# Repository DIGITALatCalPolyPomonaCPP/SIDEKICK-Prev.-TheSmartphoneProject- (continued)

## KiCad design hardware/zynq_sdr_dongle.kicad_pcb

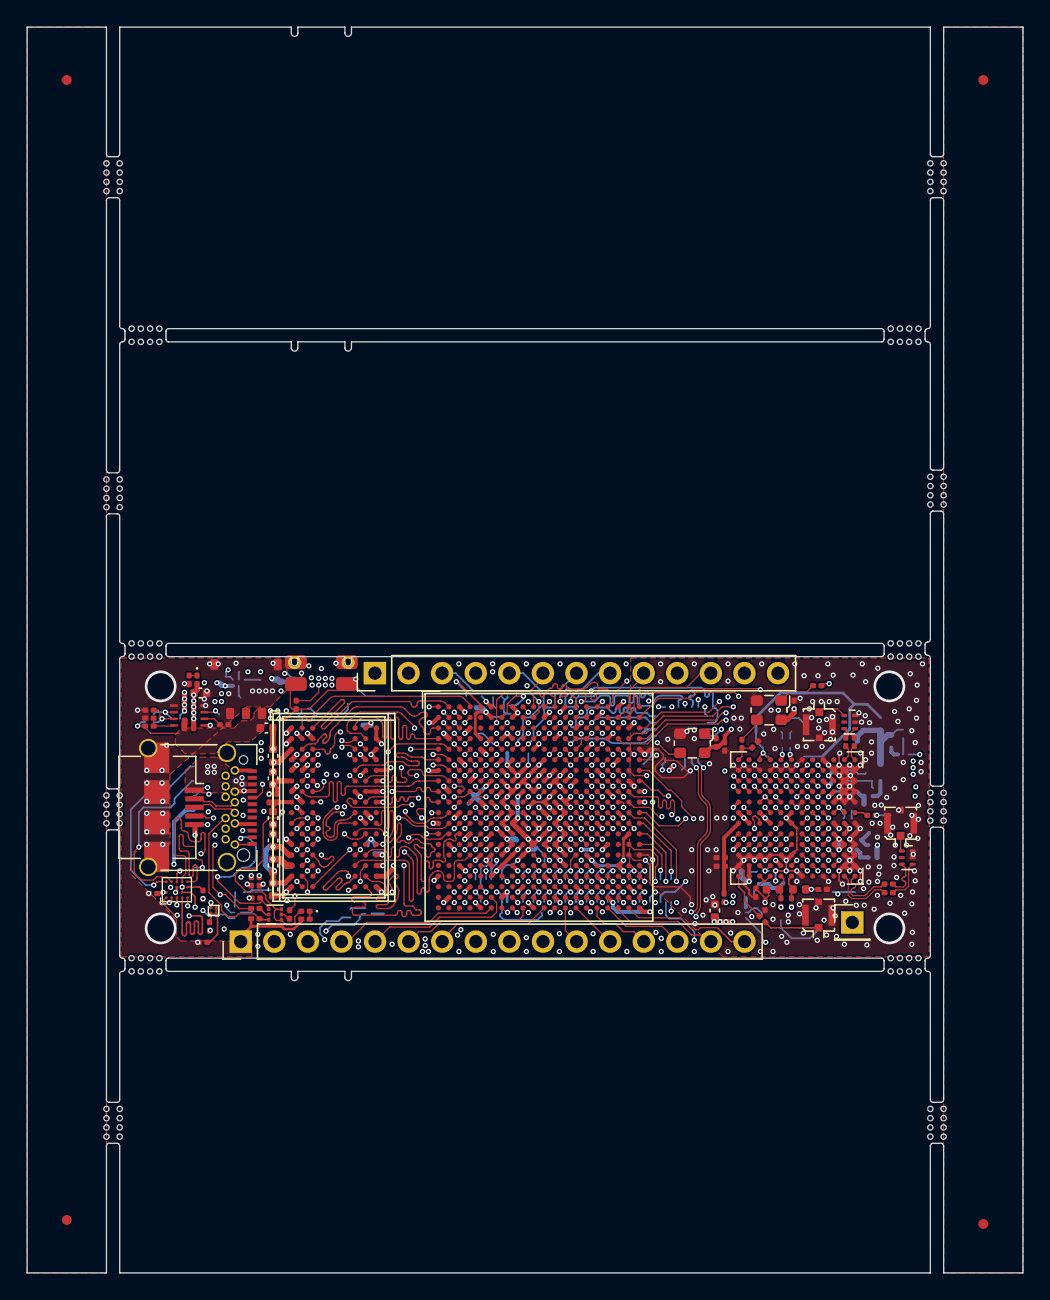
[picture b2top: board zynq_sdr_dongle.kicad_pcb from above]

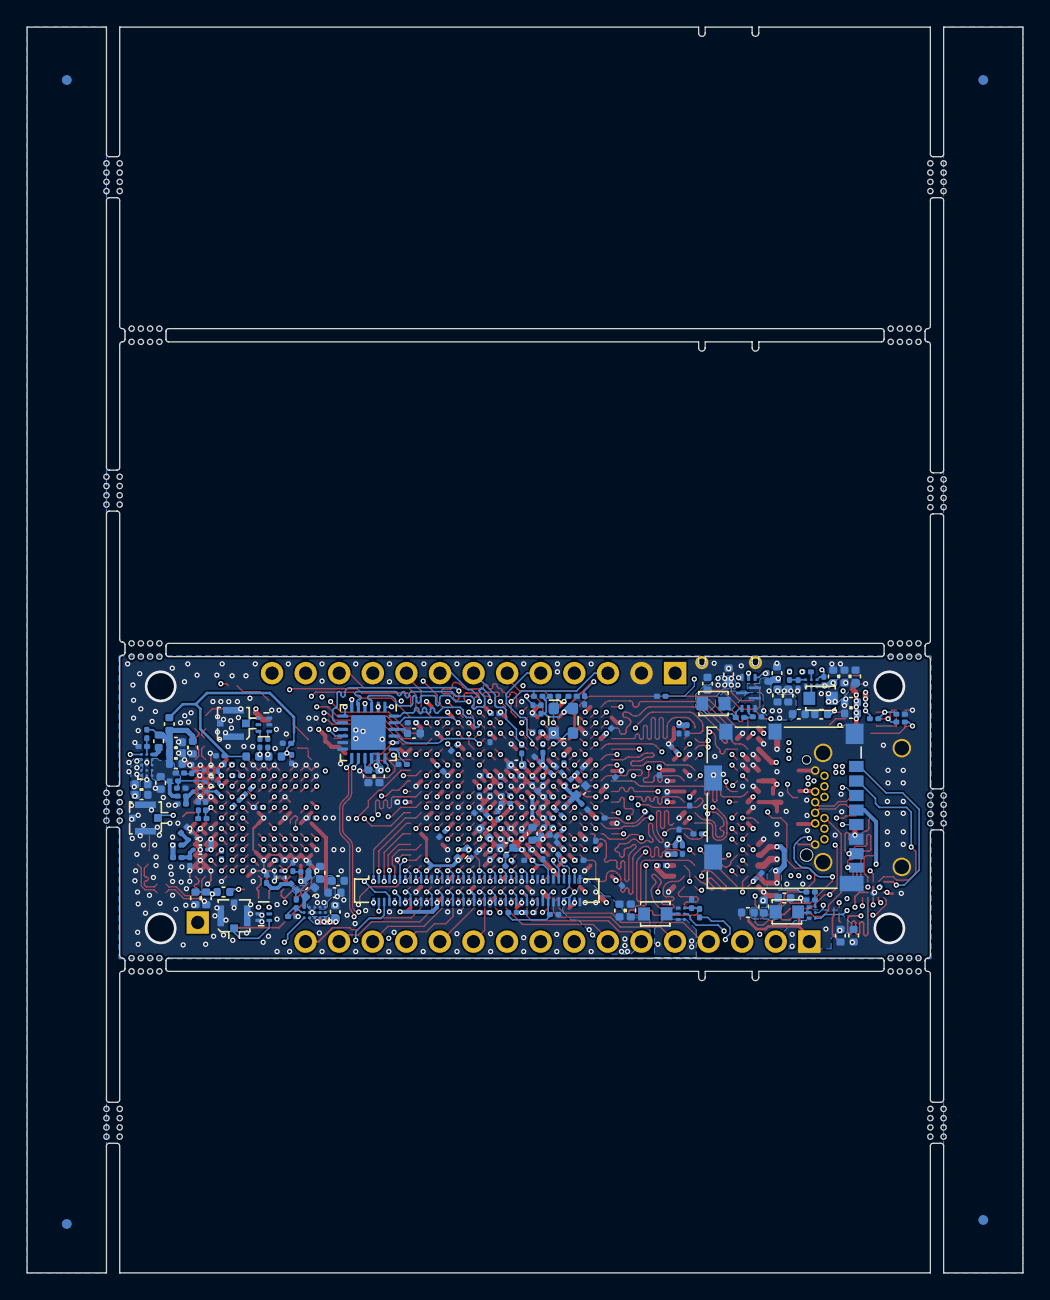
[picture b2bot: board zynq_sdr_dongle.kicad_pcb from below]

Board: 6 copper layers, 75.3 x 94.2 mm, 285 parts (208 on the bottom side), 328 nets.

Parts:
C1, C6, C9, C12, C80, C81: 18pF; C_0201_0603Metric
C2, C10, C13, C22, C28, C29, C36, C41, C62, C63, C78, C79, C120, C124, C125: 0.1uF; C_0402_1005Metric
C3, C4, C5, C7, C8, C11, C14, C15, C16, C17, C18, C19, C20, C21, C24, C25, C26, C31, C33, C34, C38, C44, C45, C46, C47, C52, C53, C54, C55, C56, C57, C58, C59, C60, C61, C64, C65, C66, C67, C68, C69, C70, C71, C72, C73, C74, C75, C76, C77, C83, C84, C85, C86, C87, C88, C98, C99, C100, C107, C108, C109, C110, C111, C115, C116, C117, C130, C131, C132, C133, C134, C135, C136, C137, C138, C139, C140, C141, C142, C143, C144, C145, C146, C147, C148: 0.1uF; C_0201_0603Metric
C23, C27, C30, C32, C35, C37, C39, C40, C42, C43, C48, C49, C50, C51, C89, C90, C91, C92, C93, C94, C95, C96, C97, C101, C102, C118, C119, C123, C128: 4.7uF; C_0402_1005Metric
C82, C104, C105, C112, C113, C114: NFM15PC146R0G3D; C_0402_1005Metric
C103, C106, C129: 1uF; C_0402_1005Metric
C121, C122, C126, C127: 10nF; C_0402_1005Metric
D1, D2, D3: LED; LED_0201_0603Metric
D4, D5: TVS; R_0201_0603Metric
FB1, FB9: FerriteBead_Small; C_0402_1005Metric
FB2, FB3, FB4, FB5, FB6, FB7, FB8: FerriteBead_Small; C_0201_0603Metric
FID1, FID2, FID3, FID4, FID5, FID6, FID7, FID8: Fiducial; Fiducial_0.75mm_Mask2.25mm
FL1, FL2, FL3, FL4: 0850BM14E0016; Balun_Johanson_1.6x0.8mm
J1: USB_C_Receptacle; USB_C_Receptacle_Amphenol_12401548E4-2A_CircularHoles
J2: USB_B_Micro; USB_Micro-B_Amphenol_10104110_Horizontal
J3: Micro_SD_Card; microSD_HC_Molex_104031-0811
J4: 5024268012; Molex_SlimStack_502430-8010_2x40_P0.40mm_Vertical
J5, J6, J7, J8, J9, J12: Conn_Coaxial; U.FL_Molex_MCRF_73412-0110_Vertical
J10: Conn_01x13_Male; PinHeader_1x13_P2.54mm_Vertical
J11: Conn_01x16_Male; PinHeader_1x16_P2.54mm_Vertical
J13: Conn_01x04_Male; BM03B-ACHSS-GAN-TF
J14: Conn_01x01; PinHeader_1x01_P2.54mm_Vertical
L1, L6, L7, L8: DFE18SANR47MG0; L_Murata_LQH2MCNxxxx02_2.0x1.6mm
L2, L3, L4, L5: L; L_0402_1005Metric
Q1: Q_Dual_NMOS_PMDXB600UNE; DFN-6-1EP_1.2x1.2mm_P0.4mm_EP0.3x0.94mm_PullBack
Q2: PMCM4401VNE; WLCSP-4-X1-WLB0909-4_0.89x0.89mm_P0.5mm
R1, R4, R5: 80Ω; R_0201_0603Metric
R2, R47, R48, R55, R56, R59, R70, R71: 4.7K; R_0201_0603Metric
R3, R43: 240Ω; R_0201_0603Metric
R6, R37: 23.7K; R_0201_0603Metric
R7, R30, R38: 5K; R_0201_0603Metric
R8, R19, R22, R25, R46, R49, R50, R52, R62, R65, R66, R69: 10K; R_0201_0603Metric
R9: 82K; R_0201_0603Metric
R10: 18K; R_0201_0603Metric
R11, R12, R18: 14.3K; R_0201_0603Metric
R13, R15: 360K; R_0201_0603Metric
R14, R16: 300K; R_0201_0603Metric
R17: 8.06K; R_0201_0603Metric
R20: 200K; R_0201_0603Metric
R21: 100K; R_0201_0603Metric
R23: 51.7K; R_0201_0603Metric
R24: 41.2K; R_0201_0603Metric
R26: 22K; R_0201_0603Metric
R27: 33K; R_0201_0603Metric
R28, R53, R64, R67: 0R; R_0201_0603Metric
R29: 10.2K; R_0201_0603Metric
R31, R32, R33, R34, R35, R36, R40: 1K; R_0201_0603Metric
R39: 51.1K; R_0201_0603Metric
R41: 0R; R_0402_1005Metric
R42, R51, R54, R60, R61, R63, R68: N/A; R_0201_0603Metric
R44, R45: 500Ω; R_0201_0603Metric
R57, R58: 30R; R_0201_0603Metric
SW2: SW_DIP_x01; EVQ9P701P
U1: DDR3; BGA-96_9.0x13.0mm_Layout2x3x16_P0.8mm_NoPaste
U2: xc7z020clg400; Xilinx_CLG400_020_Delay
U3: AD9361; bga-100_10_10_1p32_0p8
U4, U9, U10: TPS62088; PowerWCSP-6
U5: USB3346; QFN-24-1EP_4x4mm_P0.5mm_EP2.6x2.6mm
U6, U7: MAX38904C; wlp-15_2p168_1p338_0p5_0p4
U8: TPS62867; VQFN-HR
U11: TPS2121; VQFN-12_2p0_2p5_0p5
U13: TXS0206A; WLCSP-20_1.609x1.994mm_Layout4x5_P0.4mm
X1, X2, X3: SiT1602B; Oscillator_SMD_ECS_2520MV-xxx-xx-4Pin_2.5x2.0mm

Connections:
+1V0: C50.1, C51.1, C52.1, C53.1, C54.1, C55.1, C56.1, C57.1, C58.1, C59.1, C60.1, C61.1, C62.1, C63.1, C64.1, C65.1, J4.74, J4.80, L7.1, R26.1, U2.G7 (VCCPINT[6]), U2.G11 (VCCBRAM[2]), U2.G13 (VCCINT[9]), U2.H10 (VCCBRAM[2]), U2.H12 (VCCINT[9]), U2.J7 (VCCPINT[6]), U2.J13 (VCCINT[9]), U2.K12 (VCCINT[9]), U2.L7 (VCCPINT[6]), U2.L13 (VCCINT[9]), U2.M12 (VCCINT[9]), U2.N7 (VCCPINT[6]), U2.N13 (VCCINT[9]), U2.P8 (VCCPINT[6]), U2.P12 (VCCINT[9]), U2.R7 (VCCPINT[6]), U2.R13 (VCCINT[9])
+1V8: C23.1, C27.1, C30.1, C32.1, C35.1, C37.1, C66.1, C67.1, C68.1, C69.1, C70.1, C71.1, C72.1, C73.1, C74.1, C75.1, C76.1, C77.1, C78.1, C79.1, C117.1, C130.1, C131.1, C132.1, C133.1, C134.1, C135.1, C138.1, C139.1, C140.1, C141.1, C142.1, C143.1, C144.1, C145.1, C146.1, C148.1, J4.67, L1.1, R20.1, R22.1, R41.1, R46.1, R47.1, R48.1, R49.1, R50.2, R59.2, R62.1, R65.1, R66.1, R69.1, R70.2, R71.2, U2.A6 (PS_MIO5_500), U2.A13 (VCCO_MIO1_501[4]), U2.B6 (VCCO_MIO0_500[2]), U2.B16 (VCCO_MIO1_501[4]), U2.C19 (VCCO_35[6]), U2.D5 (PS_MIO8_500), U2.D7 (VCCO_MIO0_500[2]), U2.D8 (PS_MIO7_500), U2.D12 (VCCO_MIO1_501[4]), U2.E15 (VCCO_MIO1_501[4]), U2.F8 (VCCPAUX[5]), U2.F18 (VCCO_35[6]), U2.G8 (VCCPLL), U2.G9 (VCCPAUX[5]), U2.H8 (VCCPAUX[5]), U2.H14 (VCCO_35[6]), U2.J9 (VCCADC_0), U2.J11 (VCCAUX[6]), U2.J17 (VCCO_35[6]), U2.K6 (VCCO_0), U2.K8 (VCCPAUX[5]), U2.K20 (VCCO_35[6]), U2.L11 (VCCAUX[6]), U2.M8 (VCCPAUX[5]), U2.M16 (VCCO_35[6]), U2.N6 (RSVDVCC3), U2.N9 (VCCAUX[6]), U2.N11 (VCCAUX[6]), U2.P10 (VCCAUX[6]), U2.R6 (RSVDVCC2), U2.R9 (VCCAUX[6]), U2.T6 (RSVDVCC1), U3.B8 (Vdd_GPO), U3.H12 (Vdd_INTERFACE), U6.A1 (IN), U6.A2 (IN), U6.A3 (IN), U6.A4 (IN), U7.A1 (IN), U7.A2 (IN), U7.A3 (IN), U7.A4 (IN), U8.8 (VOS), U13.A2 (VCCA), X1.4 (VDD), X2.4 (VDD), X3.4 (VDD)
+3V3: C96.1, C97.1, C147.1, J3.4 (VDD), J10.1, L8.1, R9.1, U13.B3 (VCCB)
+5V: C43.1, C89.1, C90.1, C91.1, C92.1, C93.1, C94.1, C95.1, C102.1, C118.1, C119.1, D1.2 (A), D3.2 (A), R8.1, R19.1, R25.1, U4.A2 (VIN), U5.16 (VBAT), U5.17 (VBUS), U8.3 (VIN), U9.A2 (VIN), U10.A1 (EN), U10.A2 (VIN), U11.1 (OUT), U11.8 (OUT)
/ARD_ANALOG0: J11.2, U2.Y7 (IO_L13P_T2_MRCC_13)
/ARD_ANALOG1: J11.4, U2.Y6 (IO_L13N_T2_MRCC_13)
/ARD_ANALOG2: J11.5, U2.W6 (IO_L22N_T3_13)
/ARD_ANALOG3: J11.6, U2.Y9 (IO_L14P_T2_SRCC_13)
/ARD_ANALOG4: J11.7, U2.Y11 (IO_L18N_T2_13)
/ARD_ANALOG5: J11.8, R60.1, U2.Y12 (IO_L20P_T3_13)
/ARD_ANALOG6: J11.9, R42.1
/ARD_ANALOG7: J11.10, R61.1
/ARD_AREF: J11.3, R54.2, R63.2
/ARD_PWM2: J11.16, U2.Y19 (IO_L17N_T2_34)
/ARD_PWM3: J11.15, U2.Y18 (IO_L17P_T2_34)
/ARD_PWM4: J11.14, U2.Y17 (IO_L7N_T1_34)
/ARD_PWM5: J11.13, U2.Y16 (IO_L7P_T1_34)
/ARD_PWM6: J11.12, U2.Y14 (IO_L8N_T1_34)
/ARD_PWM7: J11.11, U2.Y13 (IO_L20N_T3_13)
/BTB Connector/FPGA_AUXADC_N: J4.59, U2.L10 (VN_0)
/BTB Connector/FPGA_AUXADC_P: J4.61, U2.K9 (VP_0)
/BTB Connector/FPGA_JTAG_TCK: J4.71, U2.F9 (TCK_0)
/BTB Connector/FPGA_JTAG_TDI: J4.73, R71.1, U2.G6 (TDI_0)
/BTB Connector/FPGA_JTAG_TDO: J4.77, U2.F6 (TDO_0)
/BTB Connector/FPGA_JTAG_TMS: J4.75, R70.1, U2.J6 (TMS_0)
/BTB Connector/TRANS_GPO_0: J4.8, U3.B7 (GPO_0)
/BTB Connector/TRANS_GPO_1: J4.2, U3.B6 (GPO_1)
/BTB Connector/TRANS_GPO_2: J4.4, U3.B5 (GPO_2)
/BTB Connector/TRANS_GPO_3: J4.6, U3.B4 (GPO_3)
/FPGA_VREF: J4.68, R53.2, R54.1, U2.L9 (VREFP_0)
/LDO_EN: R64.2, U2.B13 (PS_MIO50_501), U6.A5 (EN), U7.A5 (EN)
/PS-SRST#: J10.3, R62.2, U2.B10 (PS_SRST_B_501)
/PS_MIO10_SCL: J10.7, R66.2, U2.E9 (PS_MIO10_500)
/PS_MIO11_SDA: J10.6, R65.2, U2.C6 (PS_MIO11_500)
/PS_MIO16_SPI_CLK: J10.9, U2.A19 (PS_MIO16_501)
/PS_MIO17_SPI_MISO: J10.10, U2.E14 (PS_MIO17_501)
/PS_MIO18_SPI_SS: J10.11, U2.B18 (PS_MIO18_501)
/PS_MIO19_SPI_MOSI: J10.8, U2.D10 (PS_MIO19_501)
/PS_MIO20_SPI_SS1: J10.12, U2.A17 (PS_MIO20_501)
/PS_MIO21_SPI_SS2: J10.13, U2.F14 (PS_MIO21_501)
/Power Manage/DCDC_PG_1V0: R25.2, U8.4 (EN), U10.B1 (PG)
/Power Manage/DCDC_PG_1V8: R19.2, U4.A1 (EN), U8.5 (PG), U9.A1 (EN)
/Power Manage/DCDC_PG_1V35: C38.1, R22.2, SW2.2, U2.C7 (PS_POR_B_500), U9.B1 (PG)
/TRANS_AUX_ADC: R61.2, U3.L5 (AUXADC)
/TRANS_AUX_DAC1: R42.2, U3.B3 (AUXDAC1)
/TRANS_AUX_DAC2: R60.2, U3.C3 (AUXDAC2)
/Transceiver Powr/RX_VCO: C6.1, R11.1, U3.G2 (RX_VCO_LDO_OUT), U3.G3 (VddA1P1_RX_VCO)
/Transceiver Powr/TX_VCO: C12.1, R12.1, U3.A11 (VddA1P1_TX_VCO), U3.B11 (TX_VCO_LDO_OUT)
/Transceiver Powr/VDDA_BB: C114.3, U3.K4 (VddA1P3_BB)
/Transceiver Powr/VDDA_DIGI_1V3: C136.1, C137.1, FB8.1, U3.F12 (VddD1P3_DIG)
/Transceiver Powr/VDDA_RX_LO: C113.3, U3.E2 (VddA1P3_RX_LO), U3.F2 (VddA1P3_RX_VCO_LDO)
/Transceiver Powr/VDDA_RX_SYNTH: C82.3, U3.J3 (VddA1P3_RX_SYNTH)
/Transceiver Powr/VDDA_RX_TX: C104.3, U3.D2 (VddA1P3_RX_RF), U3.D3 (VddA1P3_RX_TX), U3.E3 (VddA1P3_TX_LO_BUFFER)
/Transceiver Powr/VDDA_TX_LO: C112.3, U3.B9 (VddA1P3_TX_LO), U3.B10 (VddA1P3_TX_VCO_LDO)
/Transceiver Powr/VDDA_TX_SYNTH: C105.3, U3.K3 (VddA1P3_TX_SYNTH)
/Transceiver RF/EXT_SYNC: J14.1, R68.1
/Transceiver RF/TRANS_CMOS_FB_CLK: U2.K18 (IO_L12N_T1_MRCC_35), U3.F10 (FB_CLK+)
/Transceiver RF/TRANS_CMOS_RX_D0: U2.E17 (IO_L3P_T0_DQS_AD1P_35), U3.K11 (P1_D0/RX_D0-)
/Transceiver RF/TRANS_CMOS_RX_D1: U2.F16 (IO_L6P_T0_35), U3.J12 (P1_D1/RX_D0+)
/Transceiver RF/TRANS_CMOS_RX_D2: U2.J20 (IO_L17P_T2_AD5P_35), U3.K10 (P1_D2/RX_D1-)
/Transceiver RF/TRANS_CMOS_RX_D3: U2.F17 (IO_L6N_T0_VREF_35), U3.J11 (P1_D3/RX_D1+)
/Transceiver RF/TRANS_CMOS_RX_D4: U2.F20 (IO_L15N_T2_DQS_AD12N_35), U3.K9 (P1_D4/RX_D2-)
/Transceiver RF/TRANS_CMOS_RX_D5: U2.G15 (IO_L19N_T3_VREF_35), U3.J10 (P1_D5/RX_D2+)
/Transceiver RF/TRANS_CMOS_RX_D6: U2.G19 (IO_L18P_T2_AD13P_35), U3.K8 (P1_D6/RX_D3-)
/Transceiver RF/TRANS_CMOS_RX_D7: U2.G17 (IO_L16P_T2_35), U3.J9 (P1_D7/RX_D3+)
/Transceiver RF/TRANS_CMOS_RX_D8: U2.E18 (IO_L5P_T0_AD9P_35), U3.K7 (P1_D8/RX_D4-)
/Transceiver RF/TRANS_CMOS_RX_D9: U2.G18 (IO_L16N_T2_35), U3.J8 (P1_D9/RX_D4+)
/Transceiver RF/TRANS_CMOS_RX_D10: U2.E19 (IO_L5N_T0_AD9N_35), U3.J7 (P1_D10/RX_D5-)
/Transceiver RF/TRANS_CMOS_RX_D11: U2.H18 (IO_L14N_T2_AD4N_SRCC_35), U3.H8 (P1_D11/RX_D5+)
/Transceiver RF/TRANS_CMOS_RX_FRAME: U2.H17 (IO_L13N_T2_MRCC_35), U3.G8 (RX_FRAME+)
/Transceiver RF/TRANS_CMOS_TX_D0: U2.M18 (IO_L8N_T1_AD10N_35), U3.E12 (P0_D0/TX_D0-)
/Transceiver RF/TRANS_CMOS_TX_D1: U2.L17 (IO_L11N_T1_SRCC_35), U3.D11 (P0_D1/TX_D0+)
/Transceiver RF/TRANS_CMOS_TX_D2: U2.M19 (IO_L7P_T1_AD2P_35), U3.E11 (P0_D2/TX_D1-)
/Transceiver RF/TRANS_CMOS_TX_D3: U2.M15 (IO_L23N_T3_35), U3.D10 (P0_D3/TX_D1+)
/Transceiver RF/TRANS_CMOS_TX_D4: U2.K16 (IO_L24P_T3_AD15P_35), U3.E10 (P0_D4/TX_D2-)
/Transceiver RF/TRANS_CMOS_TX_D5: U2.M17 (IO_L8P_T1_AD10P_35), U3.D9 (P0_D5/TX_D2+)
/Transceiver RF/TRANS_CMOS_TX_D6: U2.J16 (IO_L24N_T3_AD15N_35), U3.E9 (P0_D6/TX_D3-)
/Transceiver RF/TRANS_CMOS_TX_D7: U2.N16 (IO_L21N_T3_DQS_AD14N_35), U3.D8 (P0_D7/TX_D3+)
/Transceiver RF/TRANS_CMOS_TX_D8: U2.L16 (IO_L11P_T1_SRCC_35), U3.E8 (P0_D8/TX_D4-)
/Transceiver RF/TRANS_CMOS_TX_D9: U2.M14 (IO_L23P_T3_35), U3.D7 (P0_D9/TX_D4+)
/Transceiver RF/TRANS_CMOS_TX_D10: U2.H15 (IO_L19P_T3_35), U3.F8 (P0_D10/TX_D5-)
/Transceiver RF/TRANS_CMOS_TX_D11: U2.K19 (IO_L10P_T1_AD11P_35), U3.E7 (P0_D11/TX_D5+)
/Transceiver RF/TRANS_CMOS_TX_FRAME: U2.J19 (IO_L10N_T1_AD11N_35), U3.G9 (TX_FRAME+)
/Transceiver RF/TRANS_CTRL_IN0: U2.L14 (IO_L22P_T3_AD7P_35), U3.C5 (CTRL_IN0)
/Transceiver RF/TRANS_CTRL_IN1: U2.L15 (IO_L22N_T3_AD7N_35), U3.C6 (CTRL_IN1)
/Transceiver RF/TRANS_CTRL_IN2: U2.J15 (IO_25_35), U3.D6 (CTRL_IN2)
/Transceiver RF/TRANS_CTRL_IN3: U2.K14 (IO_L20P_T3_AD6P_35), U3.D5 (CTRL_IN3)
/Transceiver RF/TRANS_CTRL_OUT0: U2.B20 (IO_L1N_T0_AD0N_35), U3.D4 (CTRL_OUT0)
/Transceiver RF/TRANS_CTRL_OUT1: U2.A20 (IO_L2N_T0_AD8N_35), U3.E4 (CTRL_OUT1)
/Transceiver RF/TRANS_CTRL_OUT2: U2.J14 (IO_L20N_T3_AD6N_35), U3.E5 (CTRL_OUT2)
/Transceiver RF/TRANS_CTRL_OUT3: U2.C20 (IO_L1P_T0_AD0P_35), U3.E6 (CTRL_OUT3)
/Transceiver RF/TRANS_CTRL_OUT4: U2.G20 (IO_L18N_T2_AD13N_35), U3.F6 (CTRL_OUT4)
/Transceiver RF/TRANS_CTRL_OUT5: U2.N15 (IO_L21P_T3_DQS_AD14P_35), U3.F5 (CTRL_OUT5)
/Transceiver RF/TRANS_CTRL_OUT6: U2.L20 (IO_L9N_T1_DQS_AD3N_35), U3.F4 (CTRL_OUT6)
/Transceiver RF/TRANS_CTRL_OUT7: U2.D19 (IO_L4P_T0_35), U3.G4 (CTRL_OUT7)
/Transceiver RF/TRANS_ENABLE: U2.D18 (IO_L3N_T0_DQS_AD1N_35), U3.G6 (ENABLE)
/Transceiver RF/TRANS_ENAGC: U2.J18 (IO_L14P_T2_AD4P_SRCC_35), U3.G5 (EN_AGC)
/Transceiver RF/TRANS_MRCC_CLKOUT: U2.H16 (IO_L13P_T2_MRCC_35), U3.J6 (CLK_OUT)
/Transceiver RF/TRANS_MRCC_DATA_CLK: U2.K17 (IO_L12P_T1_MRCC_35), U3.G11 (DATA_CLK+)
/Transceiver RF/TRANS_OSC_N: C81.1, X3.3 (OUT)
/Transceiver RF/TRANS_RBIAS: R18.1, U3.L4 (RBIAS)
/Transceiver RF/TRANS_RST: U2.B14 (PS_MIO47_501), U3.K5 (~RESET)
/Transceiver RF/TRANS_RXRF0_N: C108.1, FL3.3 (RF_N)
/Transceiver RF/TRANS_RXRF0_P: C107.1, FL3.4 (RF_P)
/Transceiver RF/TRANS_RXRF1_N: C116.1, FL4.3 (RF_N)
/Transceiver RF/TRANS_RXRF1_P: C115.1, FL4.4 (RF_P)
/Transceiver RF/TRANS_SPI_CLK: U2.A16 (PS_MIO24_501), U3.J5 (SPI_CLK)
/Transceiver RF/TRANS_SPI_MISO: U2.D11 (PS_MIO23_501), U3.L6 (SPI_MISO)
/Transceiver RF/TRANS_SPI_MOSI: U2.B17 (PS_MIO22_501), U3.J4 (SPI_MOSI)
/Transceiver RF/TRANS_SPI_SS: U2.F15 (PS_MIO25_501), U3.K6 (SPI_~EN)
/Transceiver RF/TRANS_SYNC: R67.1, U2.H20 (IO_L17N_T2_AD5N_35)
/Transceiver RF/TRANS_TXNRX: U2.D20 (IO_L4N_T0_35), U3.H4 (TX~RX)
/Transceiver RF/TRANS_TXRF0_N: C44.1, FL1.4 (RF_P)
/Transceiver RF/TRANS_TXRF0_P: C45.1, FL1.3 (RF_N)
/Transceiver RF/TRANS_TXRF1_N: C47.1, FL2.4 (RF_P)
/Transceiver RF/TRANS_TXRF1_P: C46.1, FL2.3 (RF_N)
/UART_RX: J10.5, U2.E8 (PS_MIO13_500)
/UART_TX: J10.4, U2.D9 (PS_MIO12_500)
/USB Connector/PS_MIO27_500_USB_RESETB: U2.D13 (PS_MIO27_501), U5.21 (~RESETB)
/USB Connector/PS_MIO29_501_USB0_DIR: U2.C13 (PS_MIO29_501), U5.24 (DIR)
/USB Connector/PS_MIO30_501_USB0_STP: U2.C15 (PS_MIO30_501), U5.23 (STP)
/USB Connector/PS_MIO31_501_USB0_NXT: U2.E16 (PS_MIO31_501), U5.2 (NXT)
/USB Connector/PS_MIO36_501_USB0_CLK: U2.A11 (PS_MIO36_501), U5.1 (CLKOUT)
/USB Connector/PS_MIO_501_USB0_D0: U2.A14 (PS_MIO32_501), U5.3 (DATA0)
/USB Connector/PS_MIO_501_USB0_D1: U2.D15 (PS_MIO33_501), U5.4 (DATA1)
/USB Connector/PS_MIO_501_USB0_D2: U2.A12 (PS_MIO34_501), U5.5 (DATA2)
/USB Connector/PS_MIO_501_USB0_D3: U2.F12 (PS_MIO35_501), U5.6 (DATA3)
/USB Connector/PS_MIO_501_USB0_D4: U2.C16 (PS_MIO28_501), U5.7 (DATA4)
/USB Connector/PS_MIO_501_USB0_D5: U2.A10 (PS_MIO37_501), U5.8 (DATA5)
/USB Connector/PS_MIO_501_USB0_D6: U2.E13 (PS_MIO38_501), U5.9 (DATA6)
/USB Connector/PS_MIO_501_USB0_D7: U2.C18 (PS_MIO39_501), U5.10 (DATA7)
/USB Connector/PWR_STA: D2.2 (A), Q1.1 (G), Q1.3 (G), U11.9 (ST)
/USB Connector/SS_SET: C129.1, U11.11 (SS)
/USB Connector/USBC_CC1: J1.A5 (CC1), Q1.4 (D), R55.2
/USB Connector/USBC_CC2: J1.B5 (CC2), Q1.6 (D), R56.2
/USB Connector/USBHS_DN: D5.1 (A1), J1.B7 (D-), J2.2 (D-), U5.14 (DM)
/USB Connector/USBHS_DP: D4.1 (A1), J1.B6 (D+), J2.3 (D+), U5.13 (DP)
/USB Connector/USBHS_ID: J2.4 (ID), R57.2, R58.2, U5.18 (ID)
/USB Connector/VBUS_ILIM: R39.1, U11.10 (ILIM)
/ZYNQ PL Part/FPGA_SRCCN_Y8: R63.1, U2.Y8 (IO_L14N_T2_SRCC_13)
/ZYNQ PL Part/PL Config/FPGA_LED_DONE: Q2.A1 (G), R59.1, U2.R11 (DONE_0)
/ZYNQ PS Part/PS Config/PS_CLK: U2.E7 (PS_CLK_500), X2.3 (OUT)
/ZYNQ PS Part/PS Config/PS_MIO4_BOOT1: R50.1, R51.2, U2.B7 (PS_MIO4_500)
/ZYNQ PS Part/PS Config/PS_MIO6_BOOT_MODE: R52.2, U2.A5 (PS_MIO6_500)
/ZYNQ PS Part/PS Config/PS_MIO40_501_SD_CLK: U2.D14 (PS_MIO40_501), U13.D2 (CLKA)
/ZYNQ PS Part/PS Config/PS_MIO41_501_SD_CMD: U2.C17 (PS_MIO41_501), U13.C1 (CMDA)
/ZYNQ PS Part/PS Config/PS_MIO42_501_SD_D0: U2.E12 (PS_MIO42_501), U13.D1 (DAT0A)
/ZYNQ PS Part/PS Config/PS_MIO43_501_SD_D1: U2.A9 (PS_MIO43_501), U13.E1 (DAT1A)
/ZYNQ PS Part/PS Config/PS_MIO44_501_SD_D2: U2.F13 (PS_MIO44_501), U13.A1 (DAT2A)
/ZYNQ PS Part/PS Config/PS_MIO45_501_SD_D3: U2.B15 (PS_MIO45_501), U13.B1 (DAT3A)
/ZYNQ PS Part/PS Config/SDIO_CLK: J3.5 (CLK), U13.D3 (CLKB)
/ZYNQ PS Part/PS Config/SDIO_CMD: J3.3 (CMD), U13.C4 (CMDB)
/ZYNQ PS Part/PS Config/SDIO_D0: J3.7 (DAT0), U13.D4 (DAT0B)
/ZYNQ PS Part/PS Config/SDIO_D1: J3.8 (DAT1), U13.E4 (DAT1B)
/ZYNQ PS Part/PS Config/SDIO_D2: J3.1 (DAT2), U13.A4 (DAT2B)
/ZYNQ PS Part/PS Config/SDIO_D3: J3.2 (DAT3/CD), U13.B4 (DAT3B)
/ZYNQ PS Part/PS DDR/DDR_A0: U1.N3 (A0), U2.N2 (PS_DDR_A0_502)
/ZYNQ PS Part/PS DDR/DDR_A1: U1.P7 (A1), U2.K2 (PS_DDR_A1_502)
/ZYNQ PS Part/PS DDR/DDR_A2: U1.P3 (A2), U2.M3 (PS_DDR_A2_502)
/ZYNQ PS Part/PS DDR/DDR_A3: U1.N2 (A3), U2.K3 (PS_DDR_A3_502)
/ZYNQ PS Part/PS DDR/DDR_A4: U1.P8 (A4), U2.M4 (PS_DDR_A4_502)
/ZYNQ PS Part/PS DDR/DDR_A5: U1.P2 (A5), U2.L1 (PS_DDR_A5_502)
/ZYNQ PS Part/PS DDR/DDR_A6: U1.R8 (A6), U2.L4 (PS_DDR_A6_502)
/ZYNQ PS Part/PS DDR/DDR_A7: U1.R2 (A7), U2.K4 (PS_DDR_A7_502)
/ZYNQ PS Part/PS DDR/DDR_A8: U1.T8 (A8), U2.K1 (PS_DDR_A8_502)
/ZYNQ PS Part/PS DDR/DDR_A9: U1.R3 (A9), U2.J4 (PS_DDR_A9_502)
/ZYNQ PS Part/PS DDR/DDR_A10: U1.L7 (A10/AP), U2.F5 (PS_DDR_A10_502)
/ZYNQ PS Part/PS DDR/DDR_A11: U1.R7 (A11), U2.G4 (PS_DDR_A11_502)
/ZYNQ PS Part/PS DDR/DDR_A12: U1.N7 (A12/~BC), U2.E4 (PS_DDR_A12_502)
/ZYNQ PS Part/PS DDR/DDR_A13: U1.T3 (A13), U2.D4 (PS_DDR_A13_502)
/ZYNQ PS Part/PS DDR/DDR_A14: U1.T7 (A14), U2.F4 (PS_DDR_A14_502)
/ZYNQ PS Part/PS DDR/DDR_BA0: U1.M2 (BA0), U2.L5 (PS_DDR_BA0_502)
/ZYNQ PS Part/PS DDR/DDR_BA1: U1.N8 (BA1), U2.R4 (PS_DDR_BA1_502)
/ZYNQ PS Part/PS DDR/DDR_BA2: U1.M3 (BA2), U2.J5 (PS_DDR_BA2_502)
/ZYNQ PS Part/PS DDR/DDR_CKE: U1.K9 (CKE), U2.N3 (PS_DDR_CKE_502)
/ZYNQ PS Part/PS DDR/DDR_DQ0: U1.E3 (DQ0), U2.E2 (PS_DDR_DQ8_502)
/ZYNQ PS Part/PS DDR/DDR_DQ1: U1.F7 (DQ1), U2.E3 (PS_DDR_DQ9_502)
/ZYNQ PS Part/PS DDR/DDR_DQ2: U1.F2 (DQ2), U2.H2 (PS_DDR_DQ13_502)
/ZYNQ PS Part/PS DDR/DDR_DQ3: U1.F8 (DQ3), U2.G3 (PS_DDR_DQ10_502)
/ZYNQ PS Part/PS DDR/DDR_DQ4: U1.H3 (DQ4), U2.J1 (PS_DDR_DQ15_502)
/ZYNQ PS Part/PS DDR/DDR_DQ5: U1.H8 (DQ5), U2.J3 (PS_DDR_DQ12_502)
/ZYNQ PS Part/PS DDR/DDR_DQ6: U1.G2 (DQ6), U2.H1 (PS_DDR_DQ14_502)
/ZYNQ PS Part/PS DDR/DDR_DQ7: U1.H7 (DQ7), U2.H3 (PS_DDR_DQ11_502)
/ZYNQ PS Part/PS DDR/DDR_DQ8: U1.D7 (DQ8), U2.C3 (PS_DDR_DQ0_502)
/ZYNQ PS Part/PS DDR/DDR_DQ9: U1.C3 (DQ9), U2.B3 (PS_DDR_DQ1_502)
/ZYNQ PS Part/PS DDR/DDR_DQ10: U1.C8 (DQ10), U2.E1 (PS_DDR_DQ7_502)
/ZYNQ PS Part/PS DDR/DDR_DQ11: U1.C2 (DQ11), U2.C1 (PS_DDR_DQ6_502)
/ZYNQ PS Part/PS DDR/DDR_DQ12: U1.A7 (DQ12), U2.D1 (PS_DDR_DQ5_502)
/ZYNQ PS Part/PS DDR/DDR_DQ13: U1.A2 (DQ13), U2.A4 (PS_DDR_DQ3_502)
/ZYNQ PS Part/PS DDR/DDR_DQ14: U1.B8 (DQ14), U2.D3 (PS_DDR_DQ4_502)
/ZYNQ PS Part/PS DDR/DDR_DQ15: U1.A3 (DQ15), U2.A2 (PS_DDR_DQ2_502)
/ZYNQ PS Part/PS DDR/DDR_DQM0: U1.E7 (LDM), U2.F1 (PS_DDR_DM1_502)
/ZYNQ PS Part/PS DDR/DDR_DQM1: U1.D3 (UDM), U2.A1 (PS_DDR_DM0_502)
/ZYNQ PS Part/PS DDR/DDR_DQS0+: U1.F3 (LDQS), U2.G2 (PS_DDR_DQS_P1_502)
/ZYNQ PS Part/PS DDR/DDR_DQS0-: U1.G3 (~LDQS), U2.F2 (PS_DDR_DQS_N1_502)
/ZYNQ PS Part/PS DDR/DDR_DQS1+: U1.C7 (UDQS), U2.C2 (PS_DDR_DQS_P0_502)
/ZYNQ PS Part/PS DDR/DDR_DQS1-: U1.B7 (~UDQS), U2.B2 (PS_DDR_DQS_N0_502)
/ZYNQ PS Part/PS DDR/DDR_ODT: U1.K1 (ODT), U2.N5 (PS_DDR_ODT_502)
/ZYNQ PS Part/PS DDR/DDR_VRN: R4.1, U2.G5 (PS_DDR_VRN_502)
/ZYNQ PS Part/PS DDR/DDR_VRP: R5.1, U2.H5 (PS_DDR_VRP_502)
/ZYNQ PS Part/PS DDR/DDR_nCAS: U1.K3 (~CAS), U2.P5 (PS_DDR_CAS_B_502)
/ZYNQ PS Part/PS DDR/DDR_nCS: U1.L2 (~CS), U2.N1 (PS_DDR_CS_B_502)
/ZYNQ PS Part/PS DDR/DDR_nRAS: U1.J3 (~RAS), U2.P4 (PS_DDR_RAS_B_502)
/ZYNQ PS Part/PS DDR/DDR_nWE: U1.L3 (~WE), U2.M5 (PS_DDR_WE_B_502)
/ZYNQ PS Part/PS DDR/VREF_DDR1: C33.1, C34.1, C36.1, R31.2, R32.1, U2.H6 (PS_DDR_VREF0_502), U2.P6 (PS_DDR_VREF1_502)
/ZYNQ PS Part/PS DDR/VREF_DDR2: C25.1, R33.2, R34.1, U1.M8 (VREFCA)
/ZYNQ PS Part/PS DDR/VREF_DDR3: C28.1, R35.2, R36.1, U1.H1 (VREFDQ)
DDR_CK+: R1.1, U1.J7 (CK), U2.L2 (PS_DDR_CKP_502)
DDR_CK-: R1.2, U1.K7 (~CK), U2.M2 (PS_DDR_CKN_502)
DDR_nRST: R2.1, U1.T2 (~RESET), U2.B4 (PS_DDR_DRST_B_502)
FPGA_L19: J4.1, U2.L19 (IO_L9P_T1_DQS_AD3P_35)
FPGA_M20: J4.3, U2.M20 (IO_L7N_T1_AD2N_35)
FPGA_N20: J4.5, U2.N20 (IO_L14P_T2_SRCC_34)
FPGA_P14: J4.10, U2.P14 (IO_L6P_T0_34)
FPGA_P15: J4.12, U2.P15 (IO_L24P_T3_34)
FPGA_P19: J4.9, U2.P19 (IO_L13N_T2_MRCC_34)
FPGA_P20: J4.7, U2.P20 (IO_L14N_T2_SRCC_34)
FPGA_R14: J4.43, U2.R14 (IO_L6N_T0_VREF_34)
FPGA_R19: J4.11, U2.R19 (IO_0_34)
FPGA_T10: J4.55, U2.T10 (IO_L1N_T0_34)
FPGA_T11: J4.51, U2.T11 (IO_L1P_T0_34)
FPGA_T12: J4.47, U2.T12 (IO_L2P_T0_34)
FPGA_T14: J4.39, U2.T14 (IO_L5P_T0_34)
FPGA_T15: J4.35, U2.T15 (IO_L5N_T0_34)
FPGA_T16: J4.31, U2.T16 (IO_L9P_T1_DQS_34)
FPGA_T17: J4.27, U2.T17 (IO_L20P_T3_34)
FPGA_T19: J4.19, U2.T19 (IO_25_34)
FPGA_T20: J4.15, U2.T20 (IO_L15P_T2_DQS_34)
FPGA_U7: J4.65, U2.U7 (IO_L11P_T1_SRCC_13)
FPGA_U10: J4.53, U2.U10 (IO_L12N_T1_MRCC_13)
FPGA_U12: J4.45, U2.U12 (IO_L2N_T0_34)
FPGA_U13: J4.41, R40.2, U2.U13 (IO_L3P_T0_DQS_PUDC_B_34)
FPGA_U14: J4.37, U2.U14 (IO_L11P_T1_SRCC_34)
FPGA_U15: J4.33, U2.U15 (IO_L11N_T1_SRCC_34)
FPGA_U17: J4.25, U2.U17 (IO_L9N_T1_DQS_34)
FPGA_U18: J4.21, U2.U18 (IO_L12P_T1_MRCC_34)
FPGA_U19: J4.17, U2.U19 (IO_L12N_T1_MRCC_34)
FPGA_U20: J4.13, U2.U20 (IO_L15N_T2_DQS_34)
FPGA_V5: J4.76, U2.V5 (IO_L6N_T0_VREF_13)
FPGA_V10: J4.56, U2.V10 (IO_L21N_T3_DQS_13)
FPGA_V11: J4.52, U2.V11 (IO_L21P_T3_DQS_13)
FPGA_V12: J4.48, U2.V12 (IO_L4P_T0_34)
FPGA_V13: J4.44, U2.V13 (IO_L3N_T0_DQS_34)
FPGA_V15: J4.36, U2.V15 (IO_L10P_T1_34)
FPGA_V16: J4.32, U2.V16 (IO_L18P_T2_34)
FPGA_V17: J4.28, U2.V17 (IO_L21P_T3_DQS_34)
FPGA_V18: J4.24, U2.V18 (IO_L21N_T3_DQS_34)
FPGA_V20: J4.16, U2.V20 (IO_L16P_T2_34)
FPGA_W8: J4.62, U2.W8 (IO_L15N_T2_DQS_13)
FPGA_W9: J4.60, U2.W9 (IO_L16N_T2_13)
FPGA_W10: J4.54, U2.W10 (IO_L16P_T2_13)
FPGA_W11: J4.50, U2.W11 (IO_L18P_T2_13)
FPGA_W13: J4.42, U2.W13 (IO_L4N_T0_34)
FPGA_W14: J4.38, U2.W14 (IO_L8P_T1_34)
FPGA_W15: J4.34, U2.W15 (IO_L10N_T1_34)
FPGA_W16: J4.30, U2.W16 (IO_L18N_T2_34)
FPGA_W18: J4.22, U2.W18 (IO_L22P_T3_34)
FPGA_W19: J4.18, U2.W19 (IO_L22N_T3_34)
FPGA_W20: J4.14, U2.W20 (IO_L16N_T2_34)
GND: C1.2, C2.2, C3.2, C4.2, C5.2, C6.2, C7.2, C8.2, C9.2, C10.2, C11.2, C12.2, C13.2, C14.2, C15.2, C16.2, C18.2, C19.2, C21.2, C22.2, C23.2, C24.2, C25.2, C26.2, C27.2, C28.2, C29.2, C30.2, C31.2, C32.2, C33.2, C34.2, C35.2, C36.2, C37.2, C38.2, C39.2, C40.2, C41.2, C42.2, C43.2, C48.2, C49.2, C50.2, C51.2, C52.2, C53.2, C54.2, C55.2, C56.2, C57.2, C58.2, C59.2, C60.2, C61.2, C62.2, C63.2, C64.2, C65.2, C66.2, C67.2, C68.2, C69.2, C70.2, C71.2, C72.2, C73.2, C74.2, C75.2, C76.2, C77.2, C78.2, C79.2, C80.1, C82.2, C83.1, C84.1, C85.1, C86.1, C87.1, C88.1, C89.2, C90.2, C91.2, C92.2, C93.2, C94.2, C95.2, C96.2, C97.2, C98.2, C99.2, C100.2, C101.2, C102.2, C103.2, C104.2, C105.2, C106.2, C109.2, C110.2, C111.2, C112.2, C113.2, C114.2, C117.2, C118.2, C119.2, C121.2, C122.2, C123.2, C125.2, C126.2, C127.2, C128.2, C129.2, C130.2, C131.2, C132.2, C133.2, C134.2, C135.2, C136.2, C137.2, C138.2, C139.2, C140.2, C141.2, C142.2, C143.2, C144.2, C145.2, C146.2, C147.2, C148.2, D4.2 (A2), D5.2 (A2), FL1.5 (GND), FL1.6 (GND), FL2.5 (GND), FL2.6 (GND), FL3.5 (GND), FL3.6 (GND), FL4.5 (GND), FL4.6 (GND), J1.A1 (GND), J1.A12 (GND), J1.B1 (GND), J1.B12 (GND), J1.S1 (SHIELD), J2.5 (GND), J2.6 (Shield), J3.6 (VSS), J3.9 (SHIELD), J4.20, J4.23, J4.29, J4.46, J4.57, J4.63, J4.69, J4.70, J4.72, J4.78, J4.79, J5.2 (Ext), J6.2 (Ext), J7.2 (Ext), J8.2 (Ext), J9.2 (Ext), J10.2, J11.1, J12.2 (Ext), J13.3, J13.4, R2.2, R3.1, R5.2, R7.1, R10.2, R14.2, R16.2, R17.2, R18.2, R21.2, R24.2, R27.2, R28.1, R30.1, R32.2, R34.2, R36.2, R38.1, R39.2, R40.1, R43.1, R44.2, R45.1, R51.1, R52.1, R53.1, R55.1, R56.1, SW2.1, U1.A9 (VSS), U1.B1 (VSSQ), U1.B3 (VSS), U1.B9 (VSSQ), U1.D1 (VSSQ), U1.D8 (VSSQ), U1.E1 (VSS), U1.E2 (VSSQ), U1.E8 (VSSQ), U1.F9 (VSSQ), U1.G1 (VSSQ), U1.G8 (VSS), U1.G9 (VSSQ), U1.J2 (VSS), U1.J8 (VSS), U1.M1 (VSS), U1.M9 (VSS), U1.P1 (VSS), U1.P9 (VSS), U1.T1 (VSS), U1.T9 (VSS), U2.A8 (GND[59]), U2.A18 (GND[59]), U2.B1 (GND[59]), U2.B8 (PS_MIO2_500), U2.B11 (GND[59]), U2.C4 (GND[59]), U2.C9 (GND[59]), U2.C14 (GND[59]), U2.D6 (PS_MIO3_500), U2.D17 (GND[59]), U2.E10 (GND[59]), U2.E20 (GND[59]), U2.F3 (GND[59]), U2.F7 (GND[59]), U2.F11 (VCCBATT_0), U2.G10 (GND[59]), U2.G12 (GND[59]), U2.G16 (GND[59]), U2.H7 (GND[59]), U2.H9 (GND[59]), U2.H11 (GND[59]), U2.H13 (GND[59]), U2.H19 (GND[59]), U2.J2 (GND[59]), U2.J8 (GND[59]), U2.J10 (GNDADC_0), U2.J12 (GND[59]), U2.K5 (GND[59]), U2.K7 (GND[59]), U2.K10 (VREFN_0), U2.K11 (GND[59]), U2.K13 (GND[59]), U2.K15 (GND[59]), U2.L8 (GND[59]), U2.L12 (GND[59]), U2.L18 (GND[59]), U2.M1 (GND[59]), U2.M7 (GND[59]), U2.M9 (DXP_0), U2.M10 (DXN_0), U2.M11 (GND[59]), U2.M13 (GND[59]), U2.N4 (GND[59]), U2.N8 (GND[59]), U2.N10 (GND[59]), U2.N12 (GND[59]), U2.N14 (GND[59]), U2.P7 (GND[59]), U2.P9 (GND[59]), U2.P11 (GND[59]), U2.P13 (GND[59]), U2.P17 (GND[59]), U2.R8 (GND[59]), U2.R12 (GND[59]), U2.R20 (GND[59]), U2.T3 (GND[59]), U2.T7 (GND[59]), U2.T13 (GND[59]), U2.U6 (GND[59]), U2.U16 (GND[59]), U2.V9 (GND[59]), U2.V19 (GND[59]), U2.W2 (GND[59]), U2.W12 (GND[59]), U2.Y5 (GND[59]), U2.Y15 (GND[59]), U3.A4 (VssA), U3.A6 (VssA), U3.B1 (VssA), U3.B2 (VssA), U3.B12 (VssA), U3.C1 (RX2C-), U3.C2 (VssA), U3.C7 (VssA), U3.C8 (VssA), U3.C9 (VssA), U3.C10 (VssA), U3.C11 (VssA), U3.C12 (VssA), U3.D1 (RX2C+), U3.D12 (VssD), U3.E1 (RX2B+), U3.F1 (RX2B-), U3.F3 (VssA), U3.F7 (VssD), U3.F9 (VssD), U3.F11 (VssD), U3.G7 (RX_FRAME-), U3.G10 (FB_CLK-), U3.G12 (VssD), U3.H1 (RX1B+), U3.H2 (VssA), U3.H3 (VssA), U3.H6 (VssA), U3.H7 (VssD), U3.H9 (TX_FRAME-), U3.H10 (VssD), U3.J1 (RX1B-), U3.J2 (VssA), U3.K1 (RX1C+), U3.K2 (VssA), U3.K12 (VssD), U3.L1 (RX1C-), U3.L2 (VssA), U3.L3 (VssA), U3.L7 (VssA), U3.L8 (VssA), U3.L9 (VssA), U3.L10 (VssA), U3.L11 (VssA), U3.L12 (VssA), U3.M4 (VssA), U3.M6 (VssA), U4.C2 (GND), U5.11 (SPK_L), U5.12 (SPK_R), U5.25 (GND), U6.B1 (GND), U6.B2 (GND), U6.B3 (GND), U6.B4 (GND), U7.B1 (GND), U7.B2 (GND), U7.B3 (GND), U7.B4 (GND), U8.1 (AGND), U8.2 (PGND), U8.6 (VSET/MODE), U9.C2 (GND), U10.C2 (GND), U11.3 (CP2), U11.12 (GND), U13.C2 (GND), U13.C3 (GND), X1.2 (GND), X2.2 (GND), X3.2 (GND)
unnamed: C1.1, R11.2
unnamed: C9.1, R12.2
unnamed: C82.1, C100.1, FB4.1
unnamed: C98.1, C104.1, FB2.1
unnamed: C99.1, C105.1, FB3.1
unnamed: C109.1, C112.1, FB5.1
unnamed: C110.1, C113.1, FB6.1
unnamed: C111.1, C114.1, FB7.1
unnamed: D1.1 (K), Q2.B1 (D)
unnamed: D2.1 (K), R44.1
unnamed: D3.1 (K), R45.2
unnamed: FL1.1 (UBP), J5.1 (In)
unnamed: FL2.1 (UBP), J6.1 (In)
unnamed: FL3.1 (UBP), J7.1 (In)
unnamed: FL4.1 (UBP), J8.1 (In)
unnamed: C17.1, J9.1 (In)
unnamed: C20.1, J12.1 (In)
unnamed: Q1.5 (S), R58.1
unnamed: Q1.2 (S), R57.1
unnamed: Q2.A2 (S), Q2.B2 (D), R43.2
unnamed: R3.2, U1.L8 (ZQ)
unnamed: R28.2, U2.M6 (CFGBVS_0)
unnamed: R48.2, U2.R10 (INIT_B_0)
unnamed: R47.2, U2.L6 (PROGRAM_B_0)
unnamed: C107.2, U3.M1 (RX1A+)
unnamed: C108.2, U3.M2 (RX1A-)
unnamed: C115.2, U3.A2 (RX2A+)
unnamed: C116.2, U3.A1 (RX2A-)
unnamed: C20.2, U3.G1 (RX_EXT_LO_IN)
unnamed: R67.2, R68.2, U3.H5 (SYNC_IN)
unnamed: C45.2, L2.2, U3.M7 (TX1A+)
unnamed: C44.2, L3.2, U3.M8 (TX1A-)
unnamed: C84.2, C85.2, C86.2, FB1.2, L2.1, L3.1, U3.M9 (TX1B+), U3.M10 (TX1B-)
unnamed: C46.2, L4.2, U3.A8 (TX2A+)
unnamed: C47.2, L5.2, U3.A7 (TX2A-)
unnamed: C83.2, C87.2, C88.2, FB9.2, L4.1, L5.1, U3.A9 (TX2B-), U3.A10 (TX2B+)
unnamed: C17.2, U3.A12 (TX_EXT_LO_IN)
unnamed: C80.2, C81.2, U3.M12 (XTALN)
unnamed: R9.2, R10.1, U4.C1 (FB)
unnamed: R8.2, U4.B1 (PG)
unnamed: L8.2, U4.B2 (SW)
unnamed: R17.1, U5.19 (RBIAS)
unnamed: U5.20 (REFCLK), X1.3 (OUT)
unnamed: C103.1, U5.22 (VDD18)
unnamed: C106.1, U5.15 (VDD33)
unnamed: C120.2, U6.C5 (BYP)
unnamed: R13.2, R14.1, U6.B5 (FB)
unnamed: C124.2, U7.C5 (BYP)
unnamed: R15.2, R16.1, U7.B5 (FB)
unnamed: R20.2, R21.1, U8.9 (FB)
unnamed: L1.2, U8.7 (SW)
unnamed: R23.2, R24.1, U9.C1 (FB)
unnamed: L6.2, U9.B2 (SW)
unnamed: R26.2, R27.1, U10.C1 (FB)
unnamed: L7.2, U10.B2 (SW)
unnamed: R6.2, R7.2, U11.5 (OV1)
unnamed: R37.2, R38.2, U11.4 (OV2)
unnamed: R29.2, R30.2, U11.6 (PR1)
unnamed: R69.2, U13.E3 (EN)
unnamed: R46.2, X1.1 (Tri-State)
unnamed: R49.2, X2.1 (Tri-State)
unnamed: R64.1, X3.1 (Tri-State)
VBUS_5V0_USB: J1.A4 (VBUS), J1.A9 (VBUS), J1.B4 (VBUS), J1.B9 (VBUS), J2.1 (VBUS), R37.1, U11.2 (IN2)
VCC_1V3_TRANS_0: C39.1, C41.1, C120.1, C121.1, C122.1, C123.1, FB1.1, FB3.2, FB4.2, FB7.2, R13.1, U6.C1 (OUT), U6.C2 (OUT), U6.C3 (OUT), U6.C4 (OUT)
VCC_1V3_TRANS_1: C40.1, C42.1, C124.1, C125.1, C126.1, C127.1, FB2.2, FB5.2, FB6.2, FB8.2, FB9.1, R15.1, U7.C1 (OUT), U7.C2 (OUT), U7.C3 (OUT), U7.C4 (OUT)
VCC_5V0_AUX: C101.1, J13.1, R6.1, R29.1, U11.7 (IN1)
VCC_BANK34: J4.26, J4.40, J4.49, J4.58, J4.66, R41.2, U2.N19 (VCCO_34[6]), U2.R15 (VCCO_34[6]), U2.T8 (VCCO_13[4]), U2.T18 (VCCO_34[6]), U2.U11 (VCCO_13[4]), U2.V14 (VCCO_34[6]), U2.W7 (VCCO_13[4]), U2.W17 (VCCO_34[6]), U2.Y10 (VCCO_13[4]), U2.Y20 (VCCO_34[6])
VCC_DDR: C2.1, C3.1, C4.1, C5.1, C7.1, C8.1, C10.1, C11.1, C13.1, C14.1, C15.1, C16.1, C18.1, C19.1, C21.1, C22.1, C24.1, C26.1, C29.1, C31.1, C48.1, C49.1, C128.1, L6.1, R4.2, R23.1, R31.1, R33.1, R35.1, U1.A1 (VDDQ), U1.A8 (VDDQ), U1.B2 (VDD), U1.C1 (VDDQ), U1.C9 (VDDQ), U1.D2 (VDDQ), U1.D9 (VDD), U1.E9 (VDDQ), U1.F1 (VDDQ), U1.G7 (VDD), U1.H2 (VDDQ), U1.H9 (VDDQ), U1.K2 (VDD), U1.K8 (VDD), U1.N1 (VDD), U1.N9 (VDD), U1.R1 (VDD), U1.R9 (VDD), U2.A3 (VCCO_DDR_502[10]), U2.D2 (VCCO_DDR_502[10]), U2.E5 (VCCO_DDR_502[10]), U2.G1 (VCCO_DDR_502[10]), U2.H4 (VCCO_DDR_502[10]), U2.L3 (VCCO_DDR_502[10]), U2.P2 (VCCO_DDR_502[10]), U2.R5 (VCCO_DDR_502[10]), U2.U1 (VCCO_DDR_502[10]), U2.V4 (VCCO_DDR_502[10])
